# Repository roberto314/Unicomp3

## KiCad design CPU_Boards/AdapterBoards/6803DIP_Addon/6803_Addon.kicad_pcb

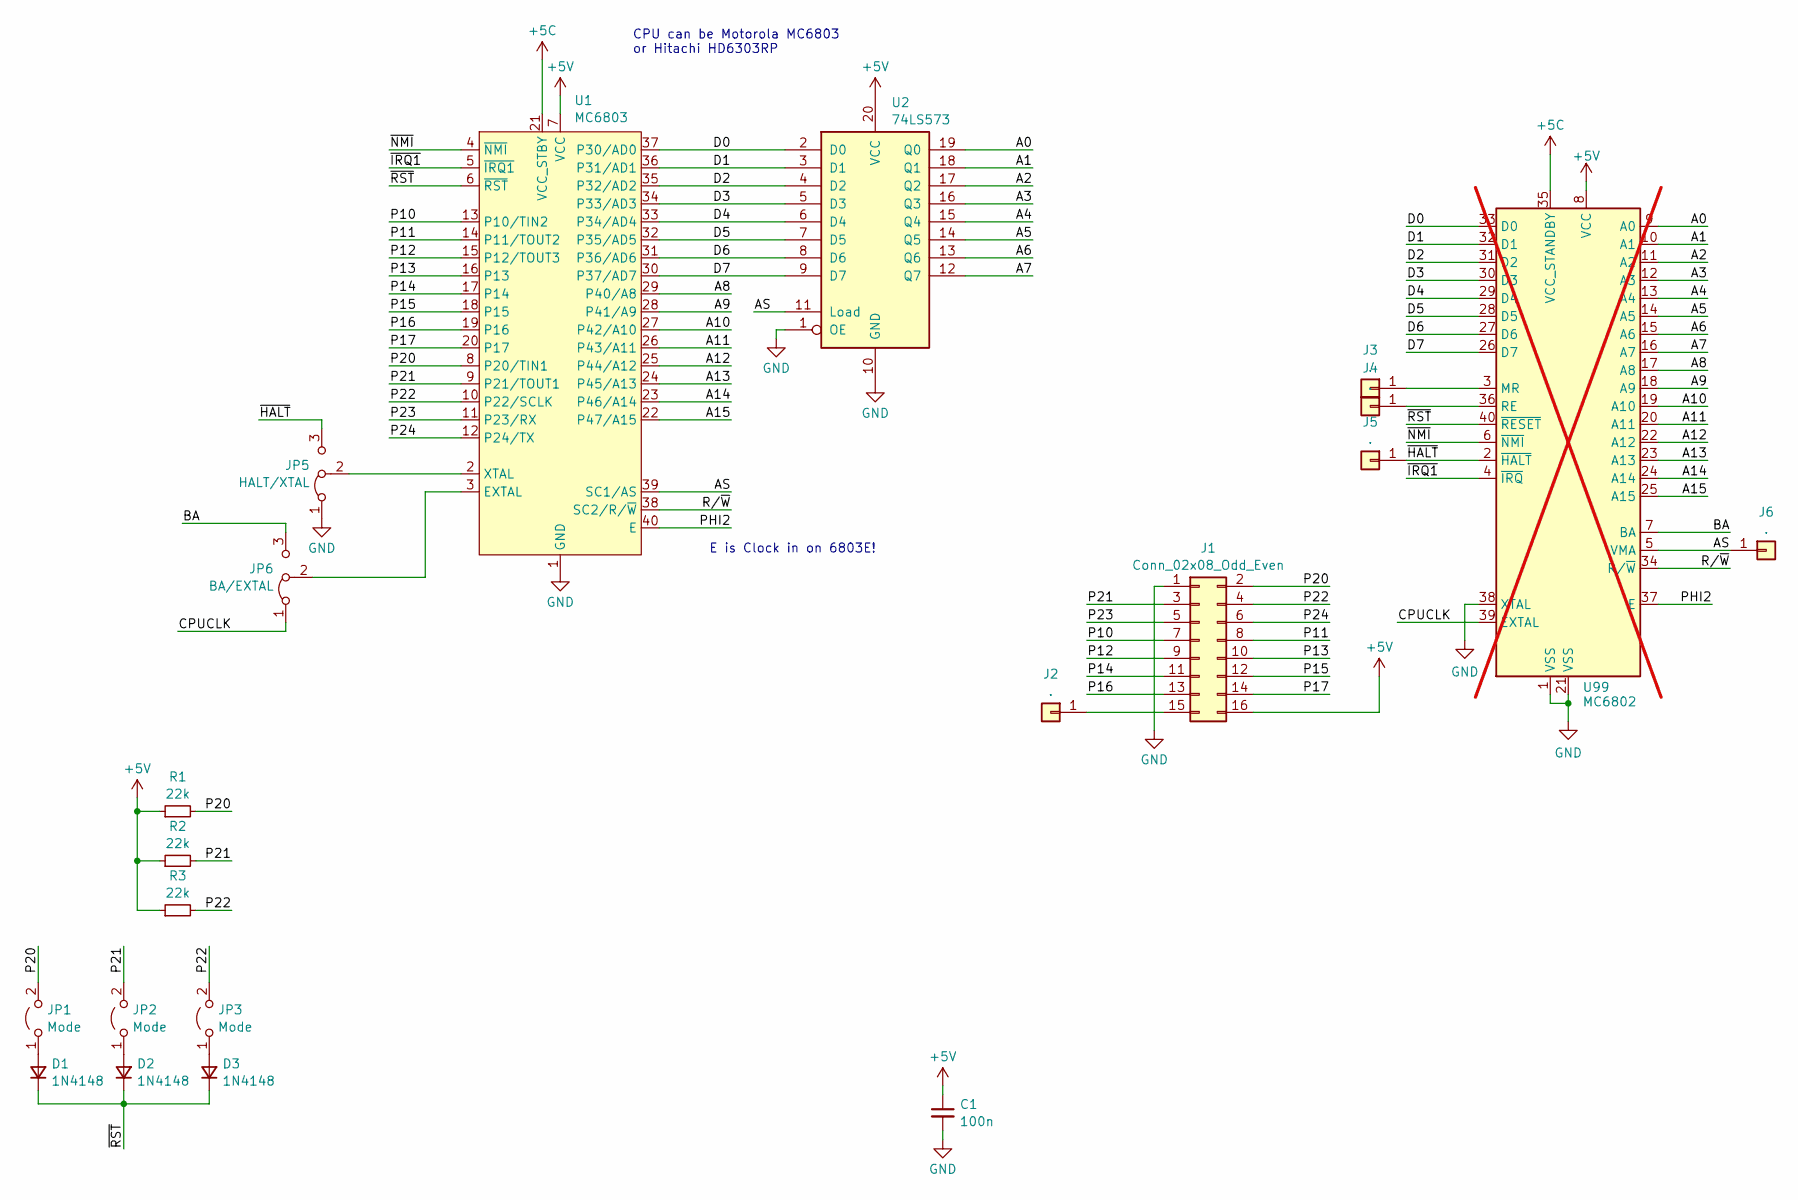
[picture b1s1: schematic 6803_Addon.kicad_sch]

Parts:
C1: 100n; C_1206_3216Metric_Pad1.33x1.80mm_HandSolder
D1, D2, D3: 1N4148; D_1206_3216Metric_Pad1.42x1.75mm_HandSolder
J1: Conn_02x08_Odd_Even; PinHeader_2x08_P2.54mm_Horizontal
J2, J3, J4, J5, J6: .; PinHeader_1x01_P2.00mm_Vertical
JP1, JP2, JP3: Mode; PinHeader_1x02_P2.54mm_Vertical
JP5: HALT/XTAL; PinHeader_1x03_P2.54mm_Vertical
JP6: BA/EXTAL; PinHeader_1x03_P2.54mm_Vertical
R1, R2, R3: 22k; R_1206_3216Metric_Pad1.30x1.75mm_HandSolder
U1: MC6803; DIP-40_W15.24mm_Socket_LongPads
U2: 74LS573; DIP-20_W7.62mm_Socket_LongPads
U99: MC6802; DIP-40_W15.24mm; not fitted

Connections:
+5C: U1.21 (VCC_STBY); also elsewhere on the board
+5V: C1.1, J1.16, R1.1, R2.1, R3.1, U1.7 (VCC), U2.20 (VCC); also elsewhere on the board
/A0: U2.19 (Q0); also elsewhere on the board
/A1: U2.18 (Q1); also elsewhere on the board
/A2: U2.17 (Q2); also elsewhere on the board
/A3: U2.16 (Q3); also elsewhere on the board
/A4: U2.15 (Q4); also elsewhere on the board
/A5: U2.14 (Q5); also elsewhere on the board
/A6: U2.13 (Q6); also elsewhere on the board
/A7: U2.12 (Q7); also elsewhere on the board
/A8: U1.29 (P40/A8); also elsewhere on the board
/A9: U1.28 (P41/A9); also elsewhere on the board
/A10: U1.27 (P42/A10); also elsewhere on the board
/A11: U1.26 (P43/A11); also elsewhere on the board
/A12: U1.25 (P44/A12); also elsewhere on the board
/A13: U1.24 (P45/A13); also elsewhere on the board
/A14: U1.23 (P46/A14); also elsewhere on the board
/A15: U1.22 (P47/A15); also elsewhere on the board
/AS: J6.1, U1.39 (SC1/AS), U2.11 (Load); also elsewhere on the board
/BA: JP6.3 (B); also elsewhere on the board
/CPUCLK: JP6.1 (A); also elsewhere on the board
/D0: U1.37 (P30/AD0), U2.2 (D0); also elsewhere on the board
/D1: U1.36 (P31/AD1), U2.3 (D1); also elsewhere on the board
/D2: U1.35 (P32/AD2), U2.4 (D2); also elsewhere on the board
/D3: U1.34 (P33/AD3), U2.5 (D3); also elsewhere on the board
/D4: U1.33 (P34/AD4), U2.6 (D4); also elsewhere on the board
/D5: U1.32 (P35/AD5), U2.7 (D5); also elsewhere on the board
/D6: U1.31 (P36/AD6), U2.8 (D6); also elsewhere on the board
/D7: U1.30 (P37/AD7), U2.9 (D7); also elsewhere on the board
/P10: J1.7, U1.13 (P10/TIN2)
/P11: J1.8, U1.14 (P11/TOUT2)
/P12: J1.9, U1.15 (P12/TOUT3)
/P13: J1.10, U1.16 (P13)
/P14: J1.11, U1.17 (P14)
/P15: J1.12, U1.18 (P15)
/P16: J1.13, U1.19 (P16)
/P17: J1.14, U1.20 (P17)
/P20: J1.2, JP1.2 (B), R1.2, U1.8 (P20/TIN1)
/P21: J1.3, JP2.2 (B), R2.2, U1.9 (P21/TOUT1)
/P22: J1.4, JP3.2 (B), R3.2, U1.10 (P22/SCLK)
/P23: J1.5, U1.11 (P23/RX)
/P24: J1.6, U1.12 (P24/TX)
/PHI2: U1.40 (E); also elsewhere on the board
/R/~W: U1.38 (SC2/R/~W); also elsewhere on the board
/~HALT: J5.1, JP5.3 (B); also elsewhere on the board
/~IRQ1: U1.5 (~IRQ1); also elsewhere on the board
/~NMI: U1.4 (~NMI); also elsewhere on the board
/~RST: D1.1 (K), D2.1 (K), D3.1 (K), U1.6 (~RST); also elsewhere on the board
GND: C1.2, J1.1, JP5.1 (A), U1.1 (GND), U2.1 (OE), U2.10 (GND); also elsewhere on the board
unnamed: D1.2 (A), JP1.1 (A)
unnamed: D2.2 (A), JP2.1 (A)
unnamed: D3.2 (A), JP3.1 (A)
unnamed: J1.15, J2.1
unnamed 53: J3.1; also elsewhere on the board
unnamed 54: J4.1; also elsewhere on the board
unnamed: JP5.2 (C), U1.2 (XTAL)
unnamed: JP6.2 (C), U1.3 (EXTAL)

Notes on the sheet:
E is Clock in on 6803E!
CPU can be Motorola MC6803 or Hitachi HD6303RP

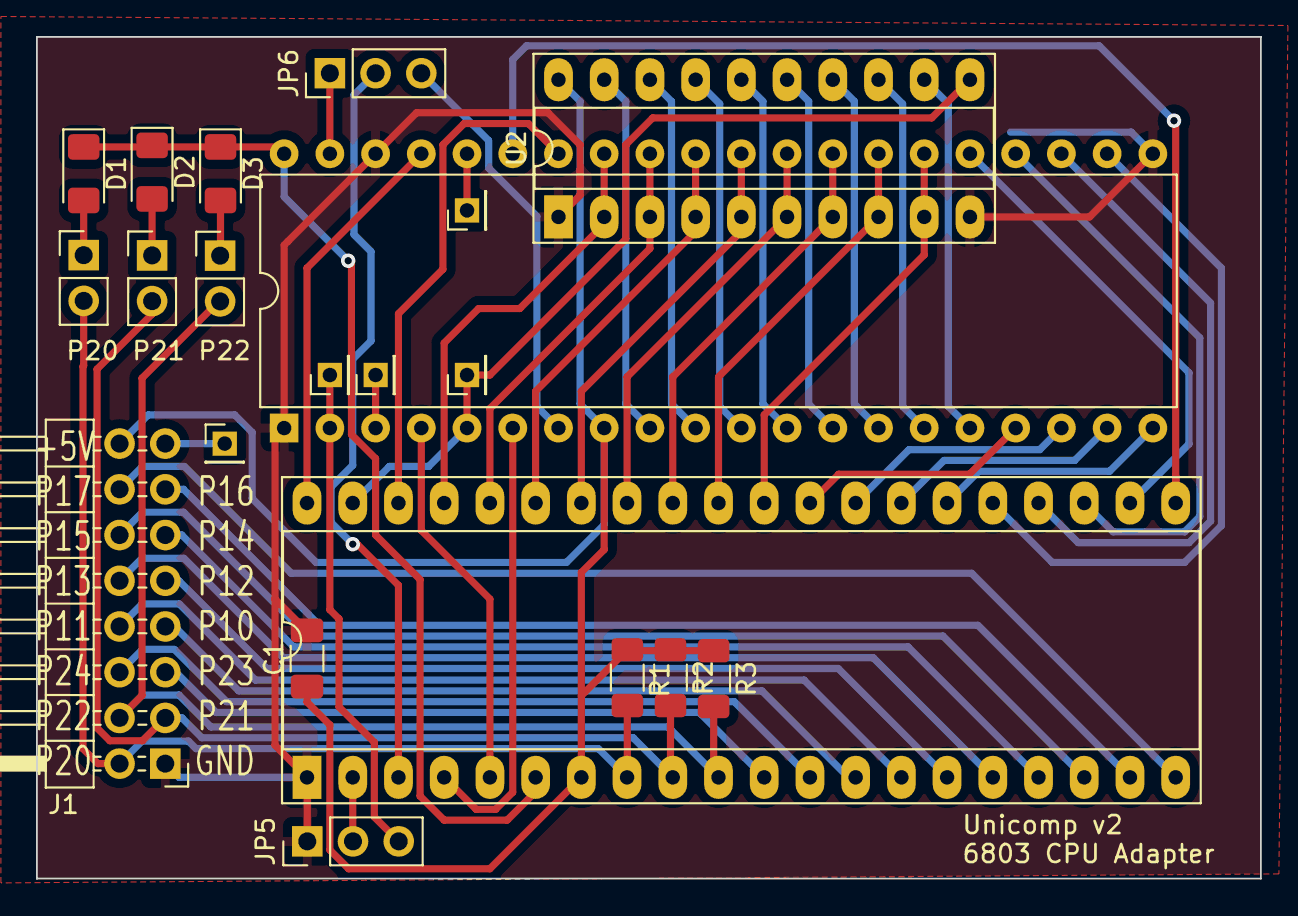
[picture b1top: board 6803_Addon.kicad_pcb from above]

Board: 2 copper layers, 68.0 x 46.8 mm, 21 parts (0 on the bottom side), 57 nets.

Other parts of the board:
U3: MC6802; DIP-40_W15.24mm

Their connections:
+5C: U3.35 (VCC_STANDBY); also elsewhere on the board
+5V: U3.8 (VCC); also elsewhere on the board
/A0: U3.9 (A0); also elsewhere on the board
/A1: U3.10 (A1); also elsewhere on the board
/A2: U3.11 (A2); also elsewhere on the board
/A3: U3.12 (A3); also elsewhere on the board
/A4: U3.13 (A4); also elsewhere on the board
/A5: U3.14 (A5); also elsewhere on the board
/A6: U3.15 (A6); also elsewhere on the board
/A7: U3.16 (A7); also elsewhere on the board
/A8: U3.17 (A8); also elsewhere on the board
/A9: U3.18 (A9); also elsewhere on the board
/A10: U3.19 (A10); also elsewhere on the board
/A11: U3.20 (A11); also elsewhere on the board
/A12: U3.22 (A12); also elsewhere on the board
/A13: U3.23 (A13); also elsewhere on the board
/A14: U3.24 (A14); also elsewhere on the board
/A15: U3.25 (A15); also elsewhere on the board
/AS: U3.5 (VMA); also elsewhere on the board
/BA: U3.7 (BA); also elsewhere on the board
/CPUCLK: U3.39 (EXTAL); also elsewhere on the board
/D0: U3.33 (D0); also elsewhere on the board
/D1: U3.32 (D1); also elsewhere on the board
/D2: U3.31 (D2); also elsewhere on the board
/D3: U3.30 (D3); also elsewhere on the board
/D4: U3.29 (D4); also elsewhere on the board
/D5: U3.28 (D5); also elsewhere on the board
/D6: U3.27 (D6); also elsewhere on the board
/D7: U3.26 (D7); also elsewhere on the board
/PHI2: U3.37 (E); also elsewhere on the board
/R/~W: U3.34 (R/~W); also elsewhere on the board
/~HALT: U3.2 (~HALT); also elsewhere on the board
/~IRQ1: U3.4 (~IRQ); also elsewhere on the board
/~NMI: U3.6 (~NMI); also elsewhere on the board
/~RST: U3.40 (~RESET); also elsewhere on the board
GND: U3.1 (VSS), U3.21 (VSS), U3.38 (XTAL); also elsewhere on the board
unnamed 53: U3.3 (MR); also elsewhere on the board
unnamed 54: U3.36 (RE); also elsewhere on the board

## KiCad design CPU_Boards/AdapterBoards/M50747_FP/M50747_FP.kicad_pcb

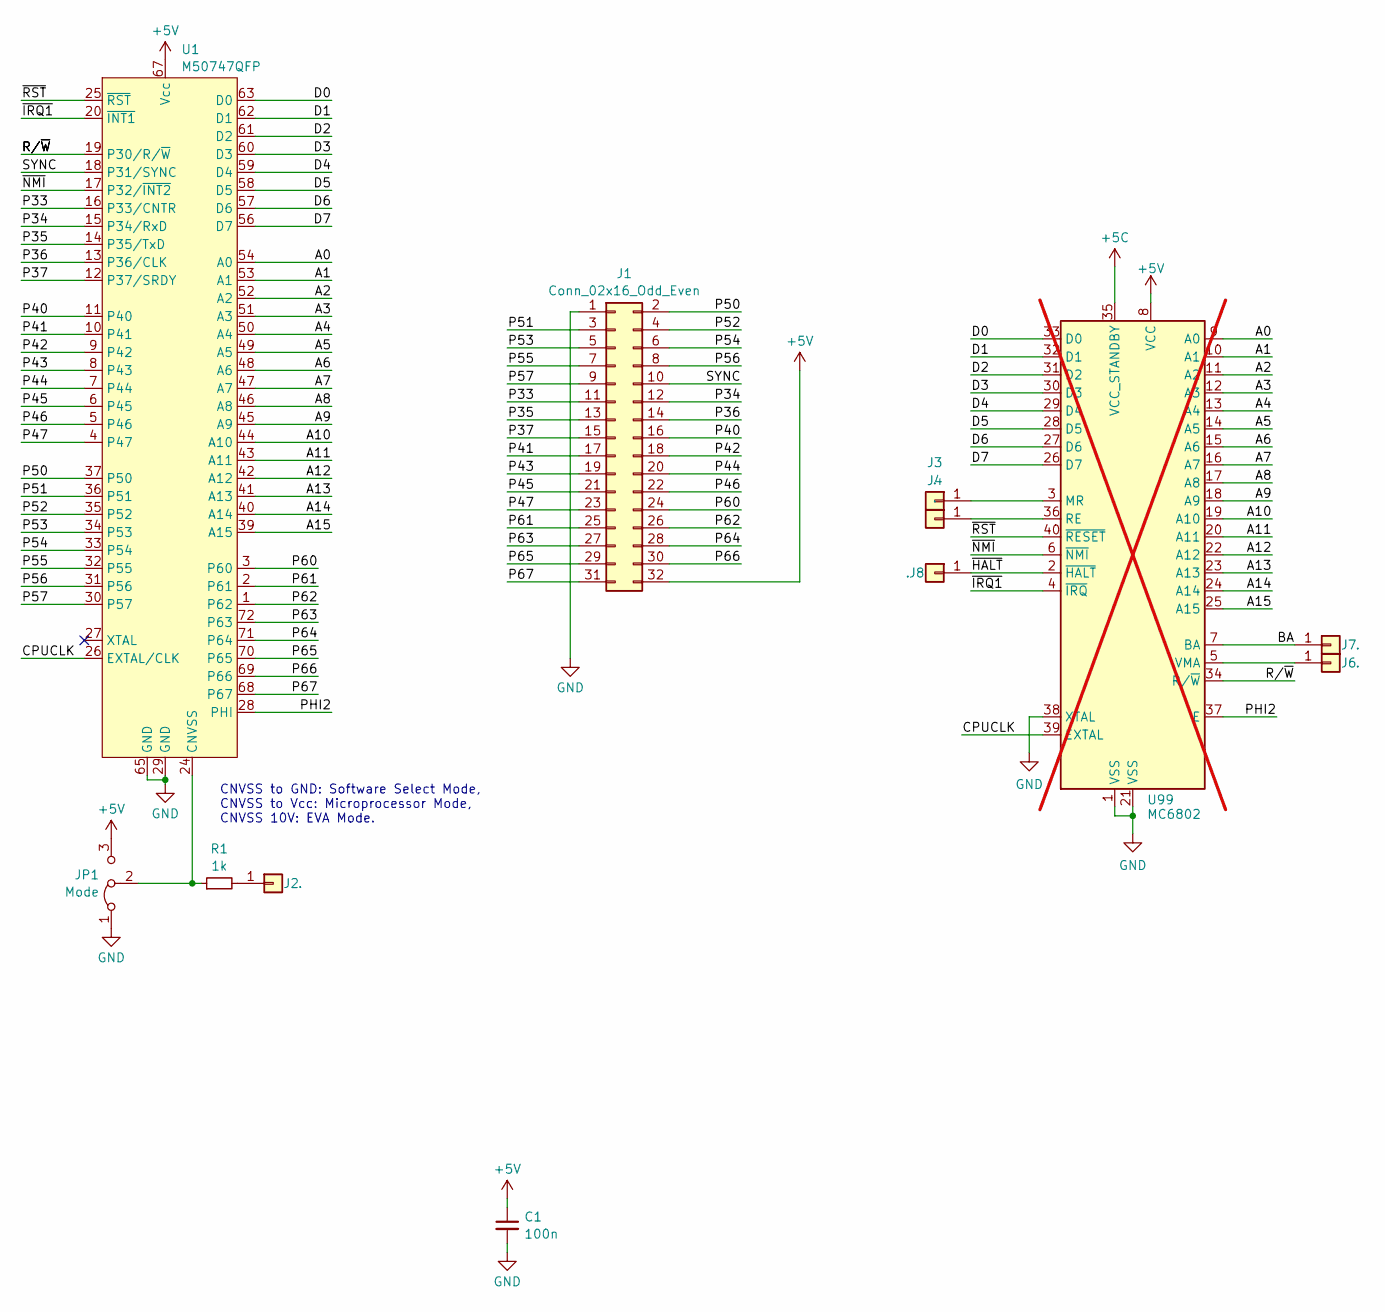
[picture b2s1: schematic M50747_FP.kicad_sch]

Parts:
C1: 100n; C_1206_3216Metric_Pad1.33x1.80mm_HandSolder
J1: Conn_02x16_Odd_Even; PinHeader_2x16_P2.54mm_Horizontal
J2, J3, J4, J6, J7, J8: .; PinHeader_1x01_P2.00mm_Vertical
JP1: Mode; SolderJumper-3_P1.3mm_Open_Pad1.0x1.5mm
R1: 1k; R_1206_3216Metric
U1: M50747QFP; QFP-72_13.2x18_Pitch0.8mm
U99: MC6802; DIP-40_W15.24mm; not fitted

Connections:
+5V: C1.1, J1.32, JP1.3 (B), U1.67 (Vcc); also elsewhere on the board
/A0: U1.54 (A0); also elsewhere on the board
/A1: U1.53 (A1); also elsewhere on the board
/A2: U1.52 (A2); also elsewhere on the board
/A3: U1.51 (A3); also elsewhere on the board
/A4: U1.50 (A4); also elsewhere on the board
/A5: U1.49 (A5); also elsewhere on the board
/A6: U1.48 (A6); also elsewhere on the board
/A7: U1.47 (A7); also elsewhere on the board
/A8: U1.46 (A8); also elsewhere on the board
/A9: U1.45 (A9); also elsewhere on the board
/A10: U1.44 (A10); also elsewhere on the board
/A11: U1.43 (A11); also elsewhere on the board
/A12: U1.42 (A12); also elsewhere on the board
/A13: U1.41 (A13); also elsewhere on the board
/A14: U1.40 (A14); also elsewhere on the board
/A15: U1.39 (A15); also elsewhere on the board
/BA: J7.1; also elsewhere on the board
/CPUCLK: U1.26 (EXTAL/CLK); also elsewhere on the board
/D0: U1.63 (D0); also elsewhere on the board
/D1: U1.62 (D1); also elsewhere on the board
/D2: U1.61 (D2); also elsewhere on the board
/D3: U1.60 (D3); also elsewhere on the board
/D4: U1.59 (D4); also elsewhere on the board
/D5: U1.58 (D5); also elsewhere on the board
/D6: U1.57 (D6); also elsewhere on the board
/D7: U1.56 (D7); also elsewhere on the board
/P33: J1.11, U1.16 (P33/CNTR)
/P34: J1.12, U1.15 (P34/RxD)
/P35: J1.13, U1.14 (P35/TxD)
/P36: J1.14, U1.13 (P36/CLK)
/P37: J1.15, U1.12 (P37/SRDY)
/P40: J1.16, U1.11 (P40)
/P41: J1.17, U1.10 (P41)
/P42: J1.18, U1.9 (P42)
/P43: J1.19, U1.8 (P43)
/P44: J1.20, U1.7 (P44)
/P45: J1.21, U1.6 (P45)
/P46: J1.22, U1.5 (P46)
/P47: J1.23, U1.4 (P47)
/P50: J1.2, U1.37 (P50)
/P51: J1.3, U1.36 (P51)
/P52: J1.4, U1.35 (P52)
/P53: J1.5, U1.34 (P53)
/P54: J1.6, U1.33 (P54)
/P55: J1.7, U1.32 (P55)
/P56: J1.8, U1.31 (P56)
/P57: J1.9, U1.30 (P57)
/P60: J1.24, U1.3 (P60)
/P61: J1.25, U1.2 (P61)
/P62: J1.26, U1.1 (P62)
/P63: J1.27, U1.72 (P63)
/P64: J1.28, U1.71 (P64)
/P65: J1.29, U1.70 (P65)
/P66: J1.30, U1.69 (P66)
/P67: J1.31, U1.68 (P67)
/PHI2: U1.28 (PHI); also elsewhere on the board
/R/~W: U1.19 (P30/R/~W); also elsewhere on the board
/SYNC: J1.10, U1.18 (P31/SYNC)
/~HALT: J8.1; also elsewhere on the board
/~IRQ1: U1.20 (~INT1); also elsewhere on the board
/~NMI: U1.17 (P32/~INT2); also elsewhere on the board
/~RST: U1.25 (~RST); also elsewhere on the board
GND: C1.2, J1.1, JP1.1 (A), U1.29 (GND), U1.65 (GND); also elsewhere on the board
unnamed: J2.1, R1.2
unnamed 66: J3.1; also elsewhere on the board
unnamed 67: J4.1; also elsewhere on the board
unnamed 68: J6.1; also elsewhere on the board
unnamed: JP1.2 (C), R1.1, U1.24 (CNVSS)

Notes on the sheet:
CNVSS to GND: Software Select Mode, CNVSS to Vcc: Microprocessor Mode, CNVSS 10V: EVA Mode.

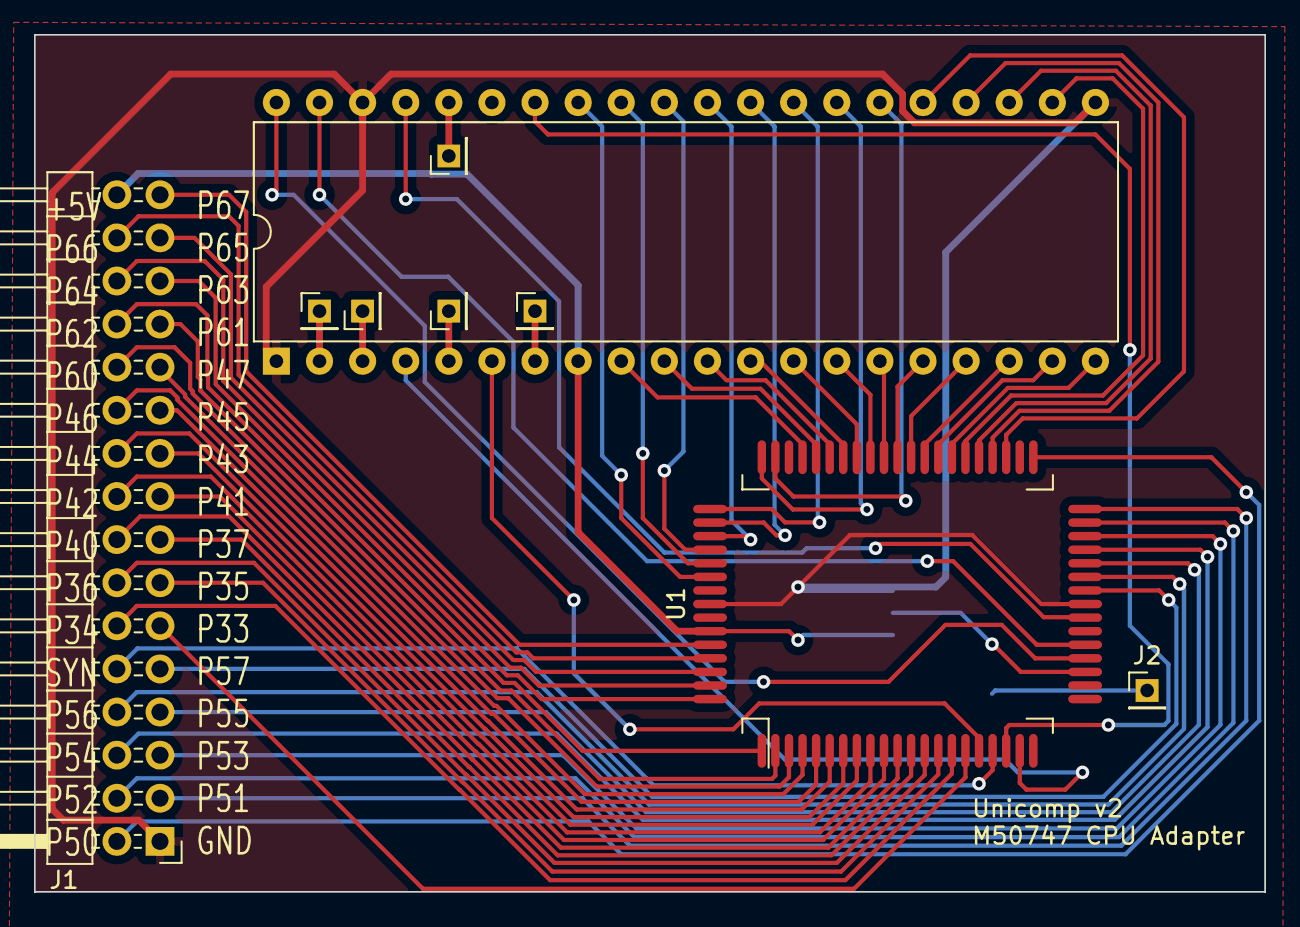
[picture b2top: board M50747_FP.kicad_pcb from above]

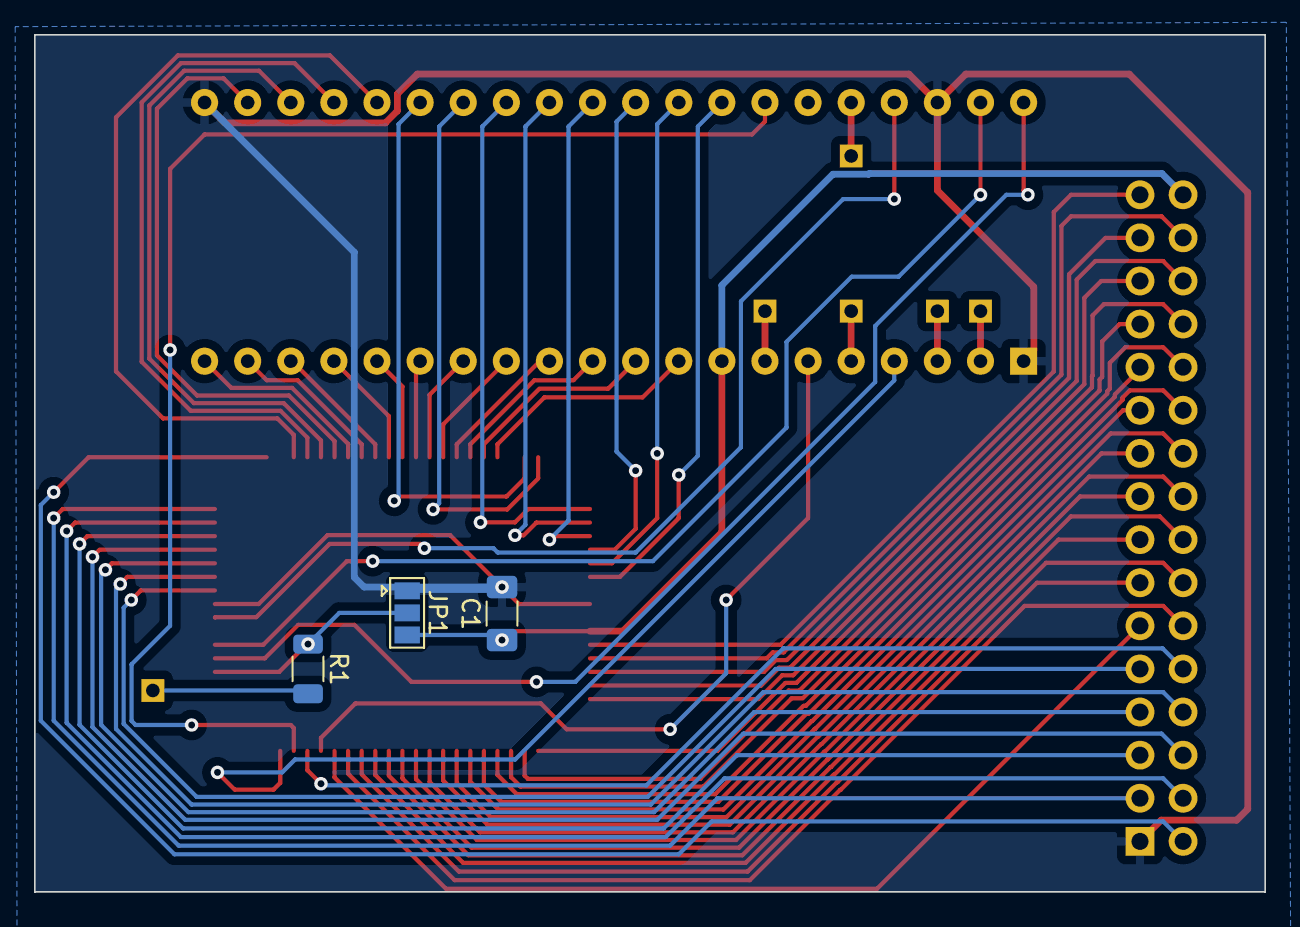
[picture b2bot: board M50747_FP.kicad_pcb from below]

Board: 2 copper layers, 72.5 x 50.5 mm, 12 parts (3 on the bottom side), 69 nets.

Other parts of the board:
U3: MC6802; DIP-40_W15.24mm

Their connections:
+5V: U3.8 (VCC); also elsewhere on the board
/A0: U3.9 (A0); also elsewhere on the board
/A1: U3.10 (A1); also elsewhere on the board
/A2: U3.11 (A2); also elsewhere on the board
/A3: U3.12 (A3); also elsewhere on the board
/A4: U3.13 (A4); also elsewhere on the board
/A5: U3.14 (A5); also elsewhere on the board
/A6: U3.15 (A6); also elsewhere on the board
/A7: U3.16 (A7); also elsewhere on the board
/A8: U3.17 (A8); also elsewhere on the board
/A9: U3.18 (A9); also elsewhere on the board
/A10: U3.19 (A10); also elsewhere on the board
/A11: U3.20 (A11); also elsewhere on the board
/A12: U3.22 (A12); also elsewhere on the board
/A13: U3.23 (A13); also elsewhere on the board
/A14: U3.24 (A14); also elsewhere on the board
/A15: U3.25 (A15); also elsewhere on the board
/BA: U3.7 (BA); also elsewhere on the board
/CPUCLK: U3.39 (EXTAL); also elsewhere on the board
/D0: U3.33 (D0); also elsewhere on the board
/D1: U3.32 (D1); also elsewhere on the board
/D2: U3.31 (D2); also elsewhere on the board
/D3: U3.30 (D3); also elsewhere on the board
/D4: U3.29 (D4); also elsewhere on the board
/D5: U3.28 (D5); also elsewhere on the board
/D6: U3.27 (D6); also elsewhere on the board
/D7: U3.26 (D7); also elsewhere on the board
/PHI2: U3.37 (E); also elsewhere on the board
/R/~W: U3.34 (R/~W); also elsewhere on the board
/~HALT: U3.2 (~HALT); also elsewhere on the board
/~IRQ1: U3.4 (~IRQ); also elsewhere on the board
/~NMI: U3.6 (~NMI); also elsewhere on the board
/~RST: U3.40 (~RESET); also elsewhere on the board
GND: U3.1 (VSS), U3.21 (VSS), U3.38 (XTAL); also elsewhere on the board
unnamed 66: U3.3 (MR); also elsewhere on the board
unnamed 67: U3.36 (RE); also elsewhere on the board
unnamed 68: U3.5 (VMA); also elsewhere on the board

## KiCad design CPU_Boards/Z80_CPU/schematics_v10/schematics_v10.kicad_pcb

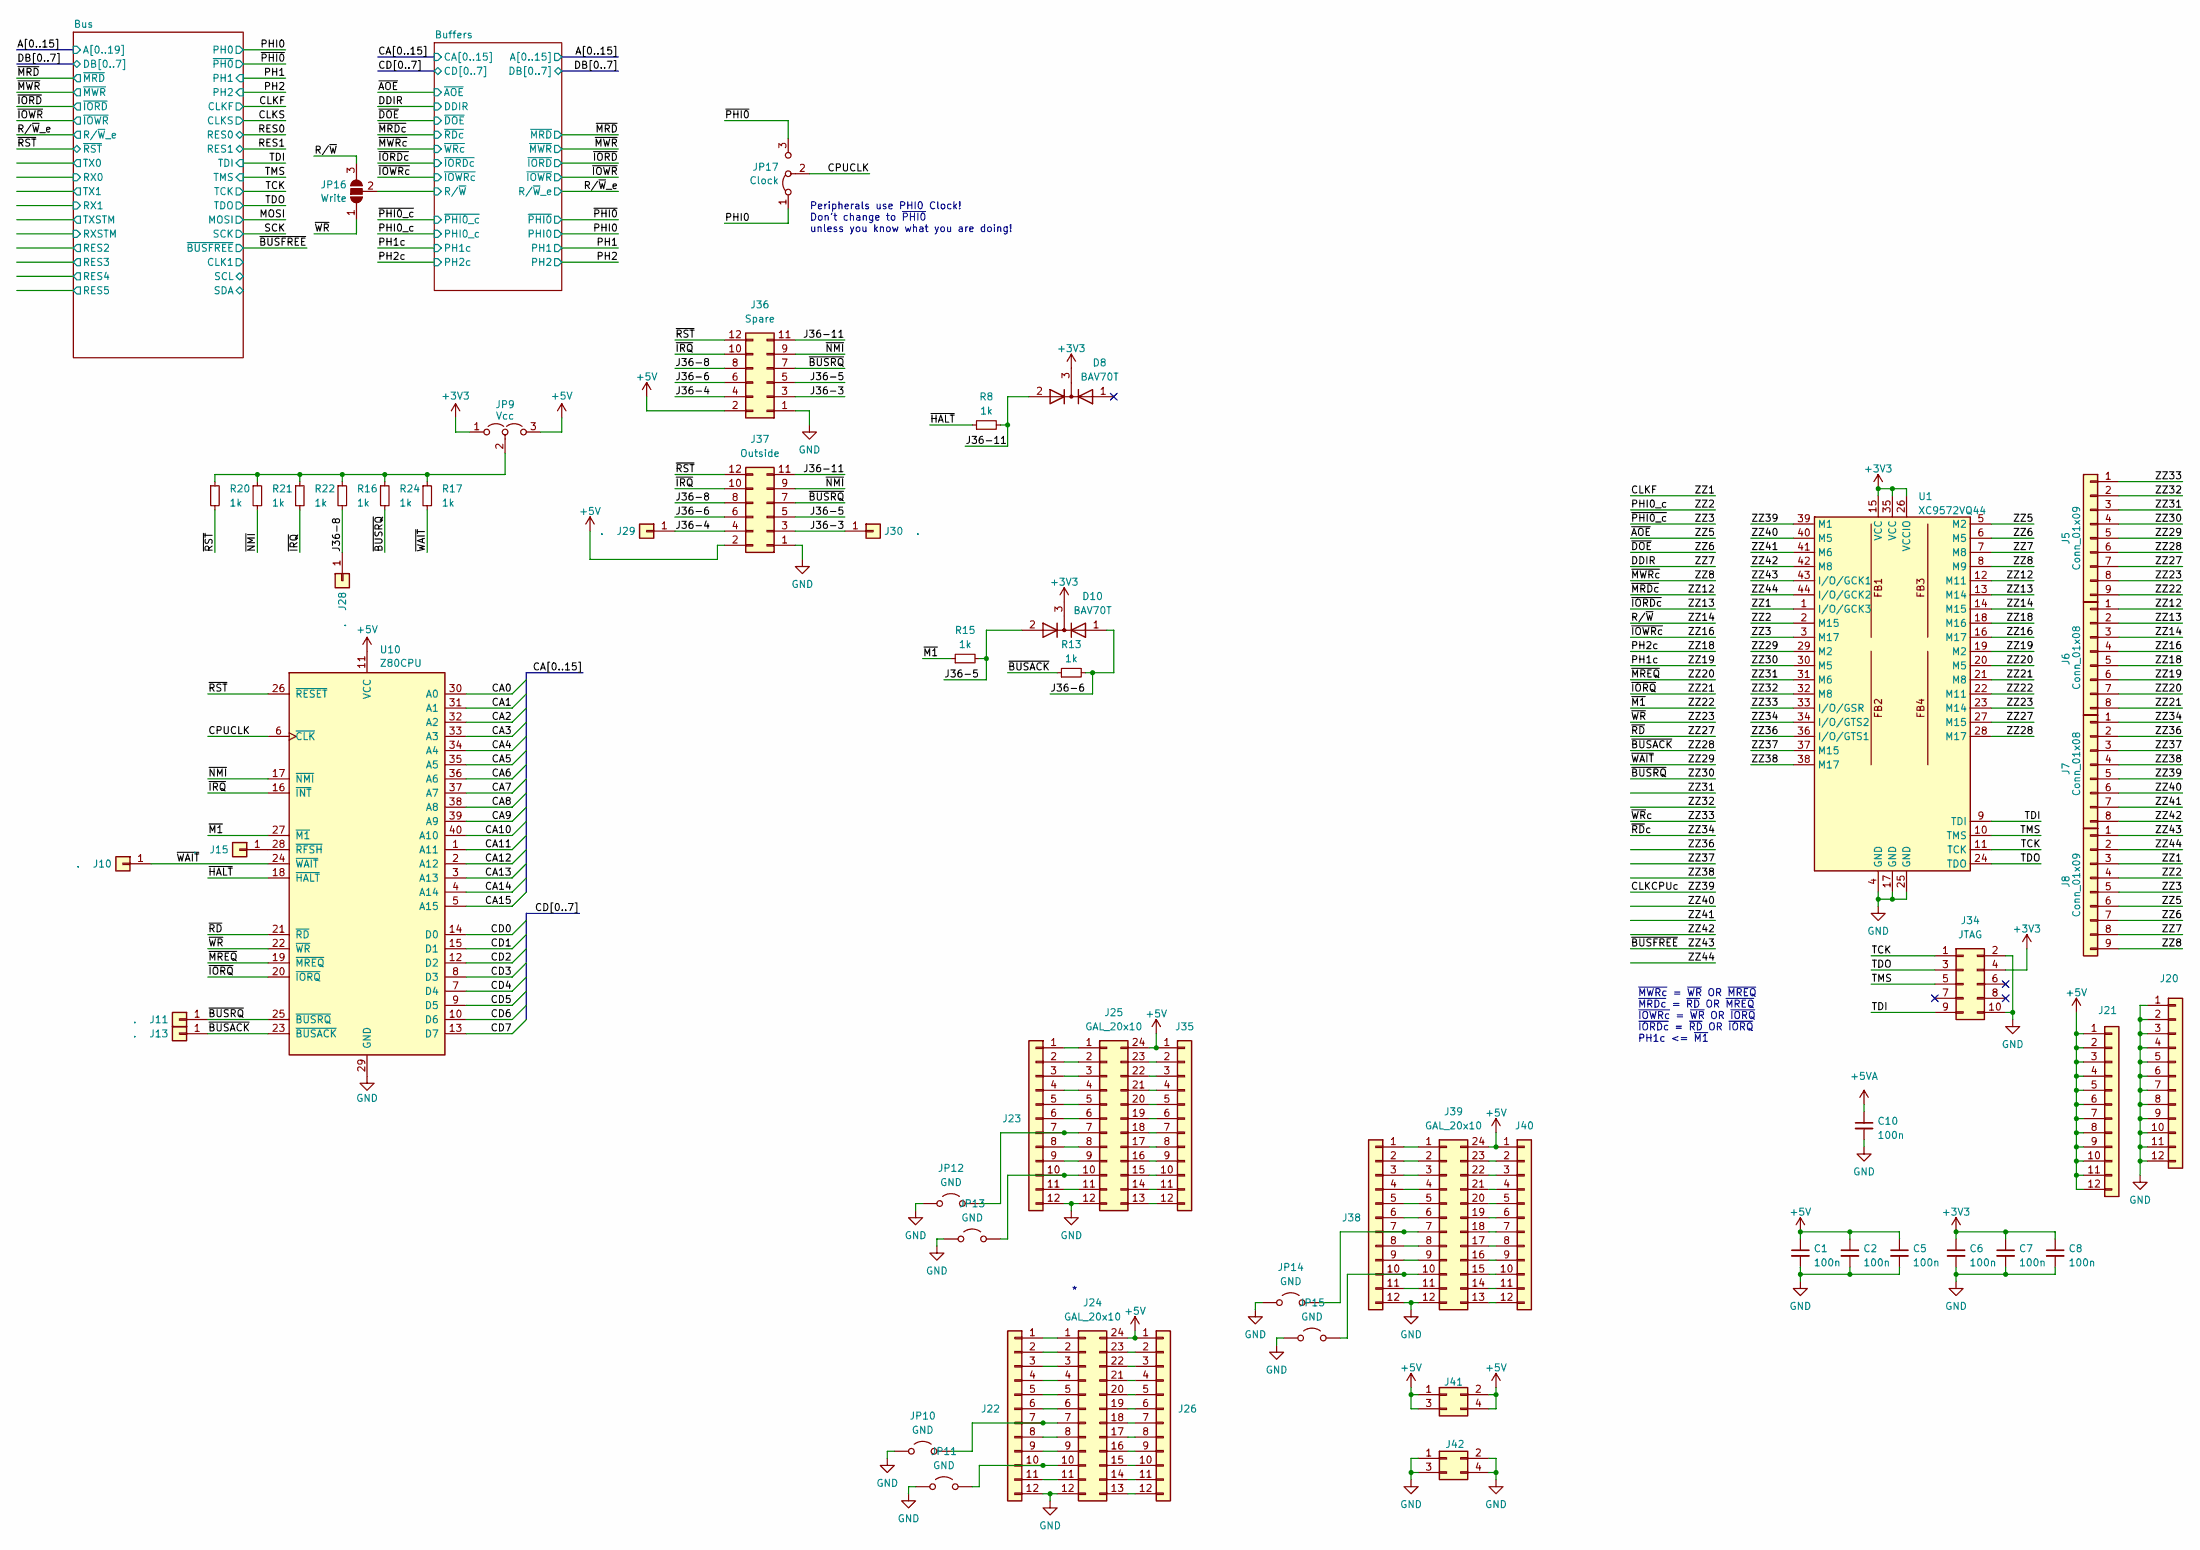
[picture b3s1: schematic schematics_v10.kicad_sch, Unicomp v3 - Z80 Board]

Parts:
C1, C2, C5, C6, C7, C8, C10: 100n; C_1206_3216Metric
D8, D10: BAV70T; SOT-23_Handsoldering
J5, J8: Conn_01x09; PinHeader_1x09_P2.54mm_Vertical
J6, J7: Conn_01x08; PinHeader_1x08_P2.54mm_Vertical
J10, J11, J13, J15, J28, J29, J30: .; PinHeader_1x01_P2.00mm_Vertical
J20, J21: Conn_01x12; PinHeader_1x12_P2.54mm_Vertical
J22, J23, J26, J35, J38, J40: Conn_01x12; PinSocket_1x12_P2.54mm_Vertical
J24, J25, J39: GAL_20x10; DIP-24_W7.62mm
J34: JTAG; PinHeader_2x05_P2.54mm_Horizontal
J36: Spare; PinHeader_2x06_P2.54mm_Vertical
J37: Outside; PinHeader_2x06_P2.54mm_Horizontal
J41, J42: Conn_02x02_Odd_Even; PinSocket_2x02_P2.54mm_Vertical
JP9: Vcc; SolderJumper-3_P1.3mm_Open_RoundedPad1.0x1.5mm_NumberLabels
JP10, JP11, JP12, JP13, JP14, JP15: GND; SolderJumper-2_P1.3mm_Open_RoundedPad1.0x1.5mm
JP16: Write; SolderJumper-3_P1.3mm_Open_RoundedPad1.0x1.5mm_NumberLabels
JP17: Clock; SolderJumper-3_P1.3mm_Bridged12_RoundedPad1.0x1.5mm
R8, R13, R15, R16, R17, R20, R21, R22, R24: 1k; R_1206_3216Metric_Pad1.30x1.75mm_HandSolder
U1: XC9572VQ44; TQFP-44_10x10mm_P0.8mm
U10: Z80CPU; DIP-40_W15.24mm_Socket_LongPads

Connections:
+3V3: C6.1, C7.1, C8.1, D8.3 (K), D10.3 (K), J34.4, JP9.1 (A), U1.15 (VCC), U1.26 (VCCIO), U1.35 (VCC); also elsewhere on the board
+5V: C1.1, C2.1, C5.1, J21.1, J21.2, J21.3, J21.4, J21.5, J21.6, J21.7, J21.8, J21.9, J21.10, J21.11, J21.12, J24.24, J25.24, J26.1, J35.1, J36.2, J37.2, J39.24, J40.1, J41.1, J41.2, J41.3, J41.4, JP9.3 (B), U10.11 (VCC); also elsewhere on the board
+5VA: C10.1; also elsewhere on the board
/Buffers/R/~W: JP16.2 (C); also elsewhere on the board
/CA0: U10.30 (A0); also elsewhere on the board
/CA1: U10.31 (A1); also elsewhere on the board
/CA2: U10.32 (A2); also elsewhere on the board
/CA3: U10.33 (A3); also elsewhere on the board
/CA4: U10.34 (A4); also elsewhere on the board
/CA5: U10.35 (A5); also elsewhere on the board
/CA6: U10.36 (A6); also elsewhere on the board
/CA7: U10.37 (A7); also elsewhere on the board
/CA8: U10.38 (A8); also elsewhere on the board
/CA9: U10.39 (A9); also elsewhere on the board
/CA10: U10.40 (A10); also elsewhere on the board
/CA11: U10.1 (A11); also elsewhere on the board
/CA12: U10.2 (A12); also elsewhere on the board
/CA13: U10.3 (A13); also elsewhere on the board
/CA14: U10.4 (A14); also elsewhere on the board
/CA15: U10.5 (A15); also elsewhere on the board
/CD0: U10.14 (D0); also elsewhere on the board
/CD1: U10.15 (D1); also elsewhere on the board
/CD2: U10.12 (D2); also elsewhere on the board
/CD3: U10.8 (D3); also elsewhere on the board
/CD4: U10.7 (D4); also elsewhere on the board
/CD5: U10.9 (D5); also elsewhere on the board
/CD6: U10.10 (D6); also elsewhere on the board
/CD7: U10.13 (D7); also elsewhere on the board
/CLKCPUc: J7.5, U1.39 (M1)
/CLKF: J8.3, U1.1 (I/O/GCK3); also elsewhere on the board
/CPUCLK: JP17.2 (C), U10.6 (~CLK)
/DDIR: J8.8, U1.7 (M8); also elsewhere on the board
/J36-3: J30.1, J36.3, J37.3
/J36-4: J29.1, J36.4, J37.4
/J36-5: D10.2 (A), J36.5, J37.5, R15.2
/J36-6: D10.1 (A), J36.6, J37.6, R13.2
/J36-8: J28.1, J36.8, J37.8, R16.2
/J36-11: D8.2 (A), J36.11, J37.11, R8.2
/PH1c: J6.6, U1.19 (M2); also elsewhere on the board
/PH2c: J6.5, U1.18 (M16); also elsewhere on the board
/PHI0: JP17.1 (A); also elsewhere on the board
/PHI0_c: J8.4, U1.2 (M15); also elsewhere on the board
/R/~W: J6.3, JP16.3 (B), U1.14 (M15)
/TCK: J34.1, U1.11 (TCK)
/TDI: J34.9, U1.9 (TDI)
/TDO: J34.3, U1.24 (TDO)
/TMS: J34.5, U1.10 (TMS)
/ZZ3: J8.5, U1.3 (M17); also elsewhere on the board
/ZZ5: J8.6, U1.5 (M2); also elsewhere on the board
/ZZ6: J8.7, U1.6 (M5); also elsewhere on the board
/ZZ8: J8.9, U1.8 (M9); also elsewhere on the board
/ZZ12: J6.1, U1.12 (M11); also elsewhere on the board
/ZZ13: J6.2, U1.13 (M14); also elsewhere on the board
/ZZ16: J6.4, U1.16 (M17); also elsewhere on the board
/ZZ20: J6.7, U1.20 (M5), U10.19 (~MREQ)
/ZZ21: J6.8, U1.21 (M8), U10.20 (~IORQ)
/ZZ22: J5.9, R15.1, U1.22 (M11), U10.27 (~M1)
/ZZ23: J5.8, JP16.1 (A), U1.23 (M14), U10.22 (~WR)
/ZZ27: J5.7, U1.27 (M15), U10.21 (~RD)
/ZZ28: J5.6, J13.1, R13.1, U1.28 (M17), U10.23 (~BUSACK)
/ZZ29: J5.5, J10.1, R17.2, U1.29 (M2), U10.24 (~WAIT)
/ZZ30: J5.4, J11.1, J36.7, J37.7, R24.2, U1.30 (M5), U10.25 (~BUSRQ)
/ZZ31: J5.3, U1.31 (M6)
/ZZ32: J5.2, U1.32 (M8)
/ZZ33: J5.1, U1.33 (I/O/GSR)
/ZZ34: J7.1, U1.34 (I/O/GTS2)
/ZZ36: J7.2, U1.36 (I/O/GTS1)
/ZZ37: J7.3, U1.37 (M15)
/ZZ38: J7.4, U1.38 (M17)
/ZZ40: J7.6, U1.40 (M5)
/ZZ41: J7.7, U1.41 (M6)
/ZZ42: J7.8, U1.42 (M8)
/ZZ43: J8.1, U1.43 (I/O/GCK1); also elsewhere on the board
/ZZ44: J8.2, U1.44 (I/O/GCK2)
/~HALT: R8.1, U10.18 (~HALT)
/~IRQ: J36.10, J37.10, R22.2, U10.16 (~INT)
/~NMI: J36.9, J37.9, R21.2, U10.17 (~NMI)
/~PHI0: JP17.3 (B); also elsewhere on the board
/~RST: J36.12, J37.12, R20.2, U10.26 (~RESET); also elsewhere on the board
GND: C1.2, C2.2, C5.2, C6.2, C7.2, C8.2, C10.2, J20.1, J20.2, J20.3, J20.4, J20.5, J20.6, J20.7, J20.8, J20.9, J20.10, J20.11, J20.12, J22.12, J23.12, J24.12, J25.12, J34.2, J34.10, J36.1, J37.1, J38.12, J39.12, J42.1, J42.2, J42.3, J42.4, JP10.1 (A), JP11.1 (A), JP12.1 (A), JP13.1 (A), JP14.1 (A), JP15.1 (A), U1.4 (GND), U1.17 (GND), U1.25 (GND), U10.29 (GND); also elsewhere on the board
unnamed: J15.1, U10.28 (~RFSH)
unnamed: J22.1, J24.1
unnamed: J22.2, J24.2
unnamed: J22.3, J24.3
unnamed: J22.4, J24.4
unnamed: J22.5, J24.5
unnamed: J22.6, J24.6
unnamed: J22.7, J24.7, JP10.2 (B)
unnamed: J22.8, J24.8
unnamed: J22.9, J24.9
unnamed: J22.10, J24.10, JP11.2 (B)
unnamed: J22.11, J24.11
unnamed: J23.1, J25.1
unnamed: J23.2, J25.2
unnamed: J23.3, J25.3
unnamed: J23.4, J25.4
unnamed: J23.5, J25.5
unnamed: J23.6, J25.6
unnamed: J23.7, J25.7, JP12.2 (B)
unnamed: J23.8, J25.8
unnamed: J23.9, J25.9
unnamed: J23.10, J25.10, JP13.2 (B)
unnamed: J23.11, J25.11
unnamed: J24.13, J26.12
unnamed: J24.14, J26.11
unnamed: J24.15, J26.10
unnamed: J24.16, J26.9
unnamed: J24.17, J26.8
unnamed: J24.18, J26.7
unnamed: J24.19, J26.6
unnamed: J24.20, J26.5
unnamed: J24.21, J26.4
unnamed: J24.22, J26.3
unnamed: J24.23, J26.2
unnamed: J25.13, J35.12
unnamed: J25.14, J35.11
unnamed: J25.15, J35.10
unnamed: J25.16, J35.9
unnamed: J25.17, J35.8
unnamed: J25.18, J35.7
unnamed: J25.19, J35.6
unnamed: J25.20, J35.5
unnamed: J25.21, J35.4
unnamed: J25.22, J35.3
unnamed: J25.23, J35.2
unnamed: J38.1, J39.1
unnamed: J38.2, J39.2
unnamed: J38.3, J39.3
unnamed: J38.4, J39.4
unnamed: J38.5, J39.5
unnamed: J38.6, J39.6
unnamed: J38.7, J39.7, JP14.2 (B)
unnamed: J38.8, J39.8
unnamed: J38.9, J39.9
unnamed: J38.10, J39.10, JP15.2 (B)
unnamed: J38.11, J39.11
unnamed: J39.13, J40.12
unnamed: J39.14, J40.11
unnamed: J39.15, J40.10
unnamed: J39.16, J40.9
unnamed: J39.17, J40.8
unnamed: J39.18, J40.7
unnamed: J39.19, J40.6
unnamed: J39.20, J40.5
unnamed: J39.21, J40.4
unnamed: J39.22, J40.3
unnamed: J39.23, J40.2
unnamed: JP9.2 (C), R16.1, R17.1, R20.1, R21.1, R22.1, R24.1

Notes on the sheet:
~{MWRc} = ~{WR} OR ~{MREQ} ~{MRDc} = ~{RD} OR ~{MREQ} ~{IOWRc} = ~{WR} OR ~{IORQ} ~{IORDc} = ~{RD} OR ~{IORQ} PH1c <= ~{M1}
Peripherals use PHI0 Clock! Don't change to ~{PHI0} unless you know what you are doing!
